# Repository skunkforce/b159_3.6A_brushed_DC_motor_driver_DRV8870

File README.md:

# edgy_board number b159
This design is part of the [edgy board project](https://github.com/skunkforce/edgy_boards). It provides the functionality of the DC motor driver chip DRV8870.

# getting started
This repository uses submodules. After cloning use the command 

```$ git submodule update --init --recursive```

to pull the submodules before opening the project with kicad. 

# Tests
Tests can be found in [TESTS.md](TESTS.md)

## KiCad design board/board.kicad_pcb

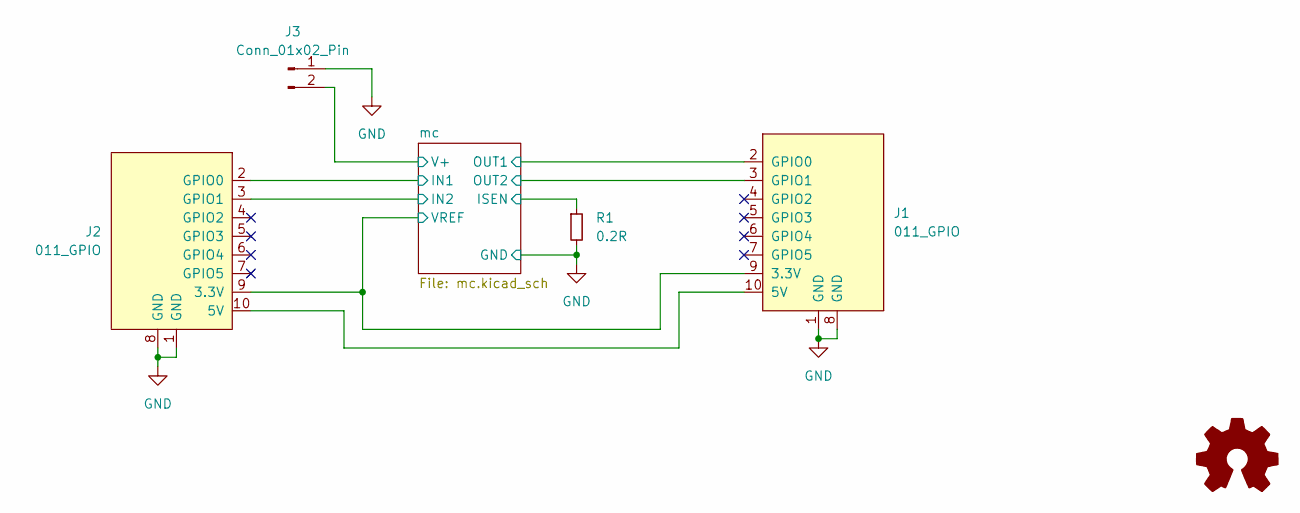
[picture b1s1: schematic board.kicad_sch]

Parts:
J1: 011_GPIO; on_edge_2x05_host
J2: 011_GPIO; on_edge_2x05_device
J3: Conn_01x02_Pin; PinHeader_1x02_P2.54mm_Vertical
LOGO1: Logo_Open_Hardware_Small; OSHW-Symbol_6.7x6mm_SilkScreen
R1: 0.2R; C_0603_1608Metric; lcsc C79773

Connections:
/mc/IN1: J2.2 (GPIO0); also elsewhere on the board
/mc/IN2: J2.3 (GPIO1); also elsewhere on the board
/mc/ISEN: R1.1; also elsewhere on the board
/mc/OUT1: J1.2 (GPIO0); also elsewhere on the board
/mc/OUT2: J1.3 (GPIO1); also elsewhere on the board
/mc/V+: J3.2; also elsewhere on the board
/mc/VREF: J1.9 (3.3V), J2.9 (3.3V); also elsewhere on the board
GND: J1.1 (GND), J1.8 (GND), J2.1 (GND), J2.8 (GND), J3.1, R1.2; also elsewhere on the board
unnamed: J1.10 (5V), J2.10 (5V)

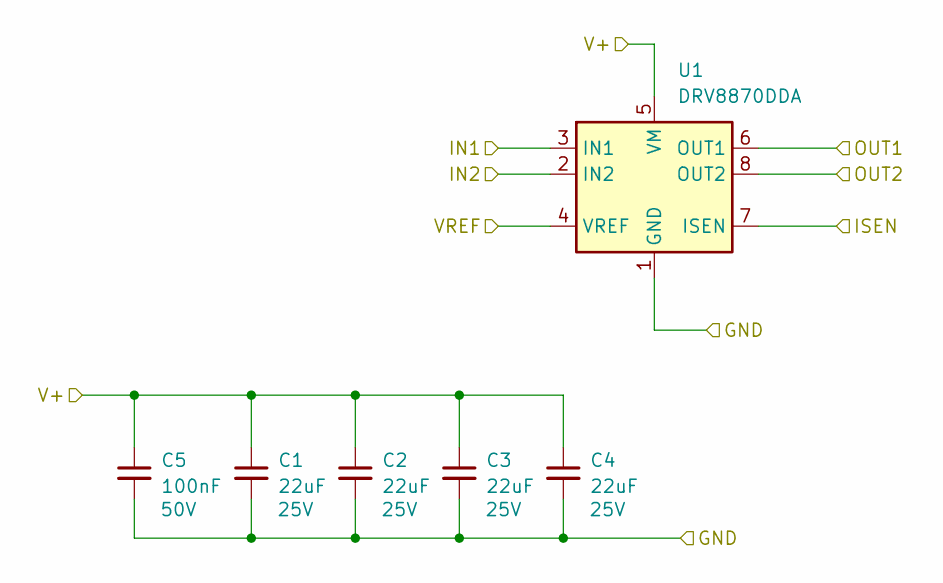
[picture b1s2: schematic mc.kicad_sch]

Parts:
C1, C2, C3, C4: 22uF; C_0805_2012Metric; Voltage 25V; lcsc C45783
C5: 100nF; C_0603_1608Metric; Voltage 50V; lcsc C14663
U1: DRV8870DDA; Texas_HTSOP-8-1EP_3.9x4.9mm_P1.27mm_EP2.95x4.9mm_Mask2.4x3.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; lcsc C86590

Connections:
/mc/IN1: U1.3 (IN1); also elsewhere on the board
/mc/IN2: U1.2 (IN2); also elsewhere on the board
/mc/ISEN: U1.7 (ISEN); also elsewhere on the board
/mc/OUT1: U1.6 (OUT1); also elsewhere on the board
/mc/OUT2: U1.8 (OUT2); also elsewhere on the board
/mc/V+: C1.1, C2.1, C3.1, C4.1, C5.1, U1.5 (VM); also elsewhere on the board
/mc/VREF: U1.4 (VREF); also elsewhere on the board
GND: C1.2, C2.2, C3.2, C4.2, C5.2, U1.1 (GND), U1.9 (GND); also elsewhere on the board

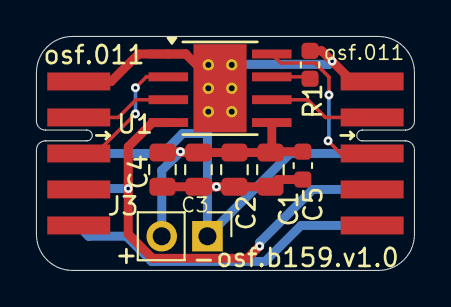
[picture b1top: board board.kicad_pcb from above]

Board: 2 copper layers, 21.0 x 13.0 mm, 11 parts (1 on the bottom side), 9 nets.

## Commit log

2025-01-18 initial
